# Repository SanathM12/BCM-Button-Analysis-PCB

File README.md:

# BCM Button Analysis PCB

A compact 2-layer PCB developed for anticipation-based clinical studies at Baylor College of Medicine. Designed for low-noise human-input capture with sub-100 ms latency and reliable USB serial output.

## Hardware Overview
- **MCU:** ATmega32U4 (native USB)
- **Inputs:**
  - BNC connectors for shielded photoresistor signal input and signal output to oscilloscope
  - Terminal blocks for buttons
- **Power:** USB 5V with onboard regulation
- **PCB:** 2-layer, KiCAD design, ~20 components assembled
- **Purpose:** Stable, low-latency human-input acquisition

## Key Features
- De-bounced and filtered input capture
- Clean analog/digital separation for noise reduction
- Robust, lab-friendly connector interfaces
- Oscilloscope-verified timing and signal integrity

## Firmware Summary
- C/C++ polling loop at regular intervals
- Detection of button presses and light-level changes
- USB serial logging with timestamps
- Reliable event timing for clinical data collection

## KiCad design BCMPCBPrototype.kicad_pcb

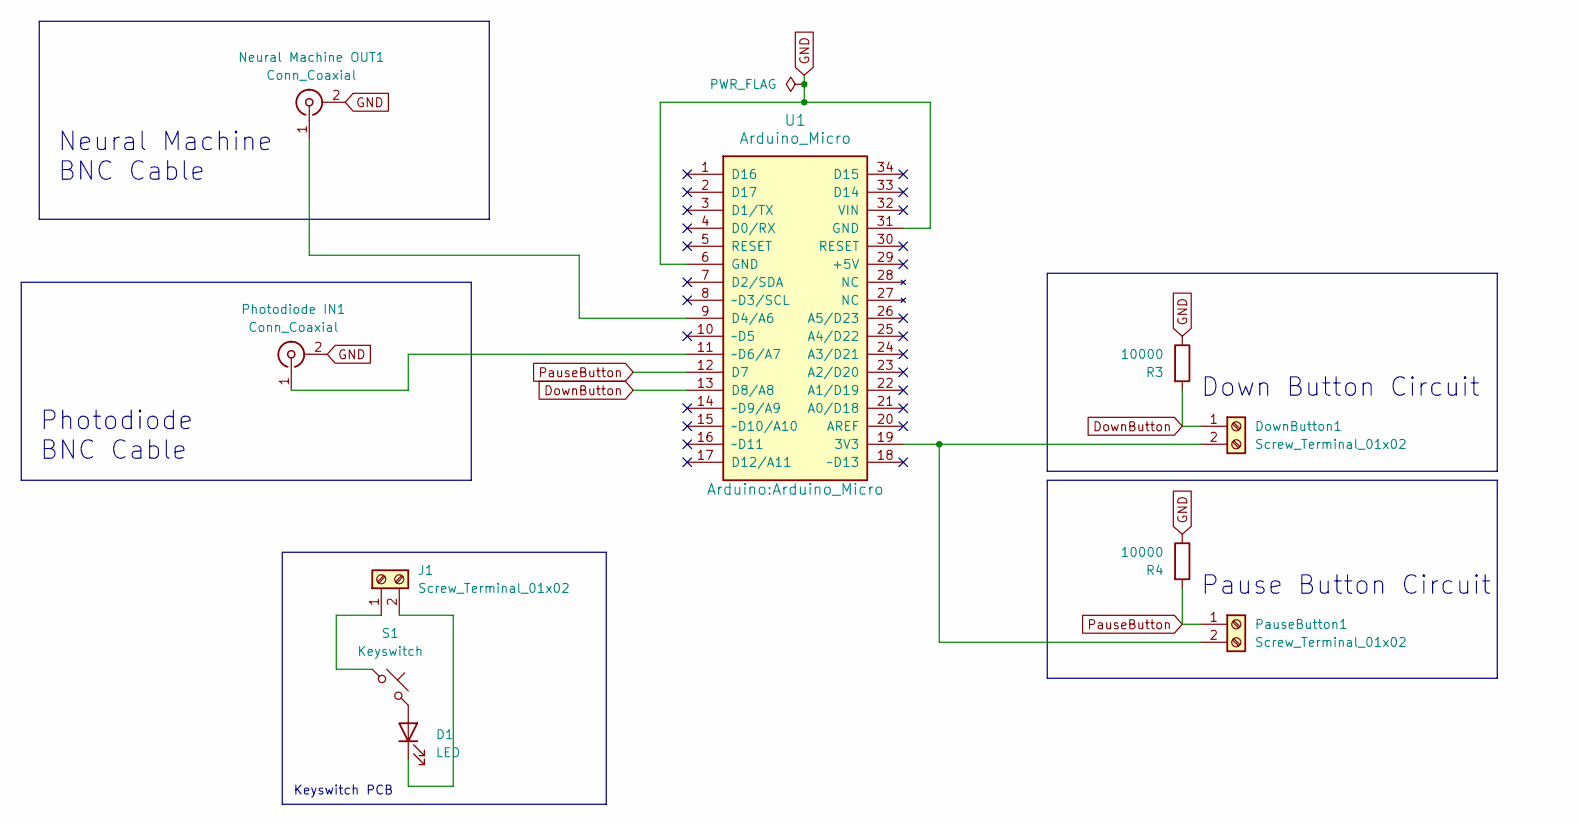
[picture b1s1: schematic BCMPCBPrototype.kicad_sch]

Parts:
D1: LED; LED_D5.0mm
DownButton1: Screw_Terminal_01x02; 1868076
J1: Screw_Terminal_01x02; PhoenixContact_MSTBA_2,5_2-G_1x02_P5.00mm_Horizontal
Neural Machine OUT1: Conn_Coaxial; RF101KD0050BKHDW
PauseButton1: Screw_Terminal_01x02; 1868076
Photodiode IN1: Conn_Coaxial; RF101KD0050BKHDW
R3, R4: 10000; R_Axial_DIN0207_L6.3mm_D2.5mm_P10.16mm_Horizontal
S1: Keyswitch; MX_PCB_1.00u_Reversable
U1: Arduino_Micro

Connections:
DownButton: DownButton1.1, R3.2, U1.13 (D8/A8)
GND: Neural Machine OUT1.2 (Ext), Photodiode IN1.2 (Ext), R3.1, R4.1, U1.6 (GND), U1.31 (GND)
unnamed: D1.2 (A), S1.2
unnamed: D1.1 (K), J1.2
unnamed: DownButton1.2, PauseButton1.2, U1.19 (3V3)
unnamed: J1.1, S1.1
unnamed: Neural Machine OUT1.1 (In), U1.9 (D4/A6)
unnamed: Photodiode IN1.1 (In), U1.11 (~D6/A7)
PauseButton: PauseButton1.1, R4.2, U1.12 (D7)

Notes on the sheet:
Photodiode BNC Cable
Pause Button Circuit
Down Button Circuit
Keyswitch PCB
Neural Machine BNC Cable

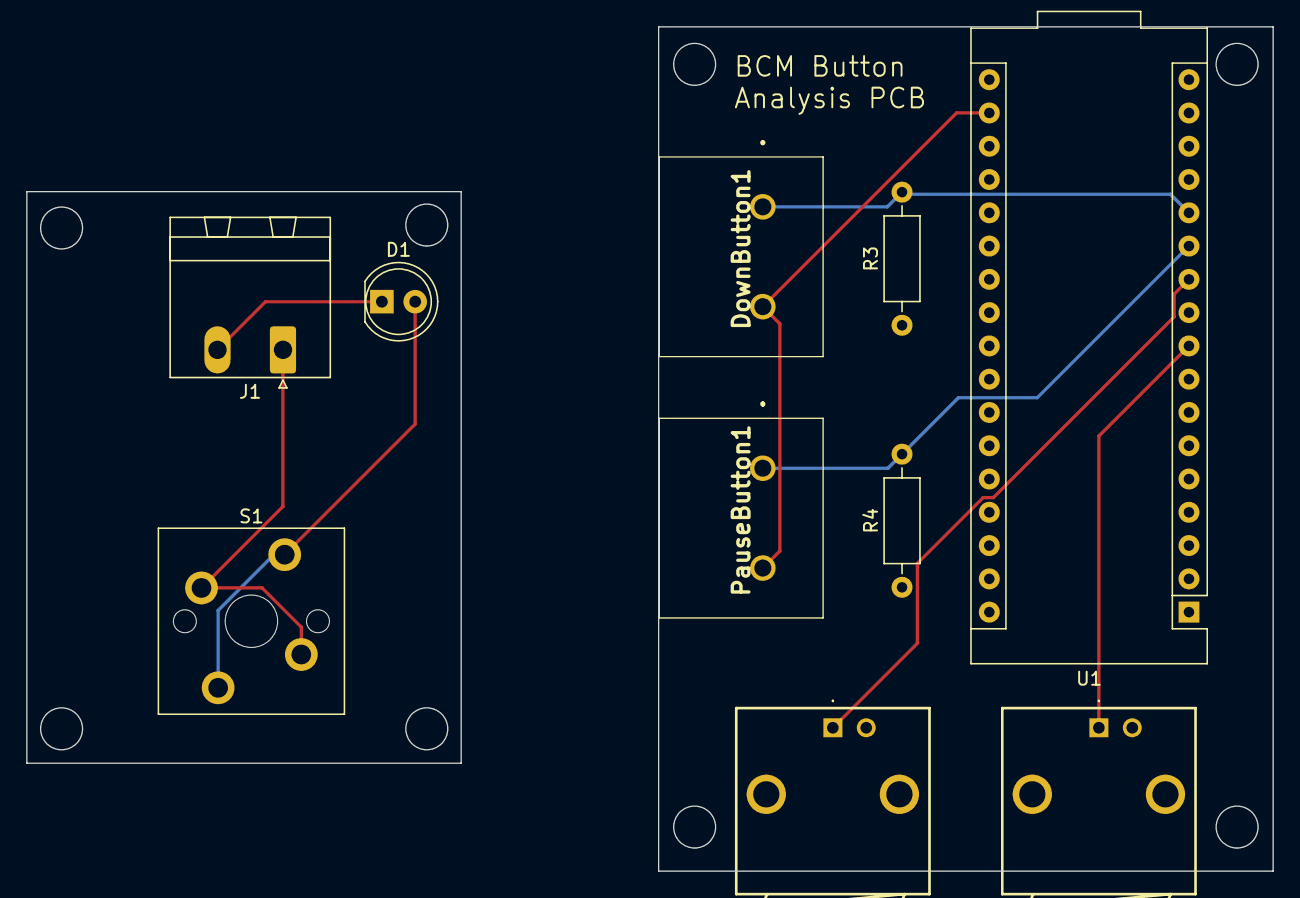
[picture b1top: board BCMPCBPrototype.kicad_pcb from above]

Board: 2 copper layers, 95.1 x 64.4 mm, 10 parts (0 on the bottom side), 9 nets.

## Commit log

2025-11-17 Major upload for BCM Button Analysis PCB
    Contains all major PCB file documentation
2025-11-17 Created README.md with images of PCB
2025-11-17 Main firmware program for BCM PCB
2025-11-17 Added description to README file
